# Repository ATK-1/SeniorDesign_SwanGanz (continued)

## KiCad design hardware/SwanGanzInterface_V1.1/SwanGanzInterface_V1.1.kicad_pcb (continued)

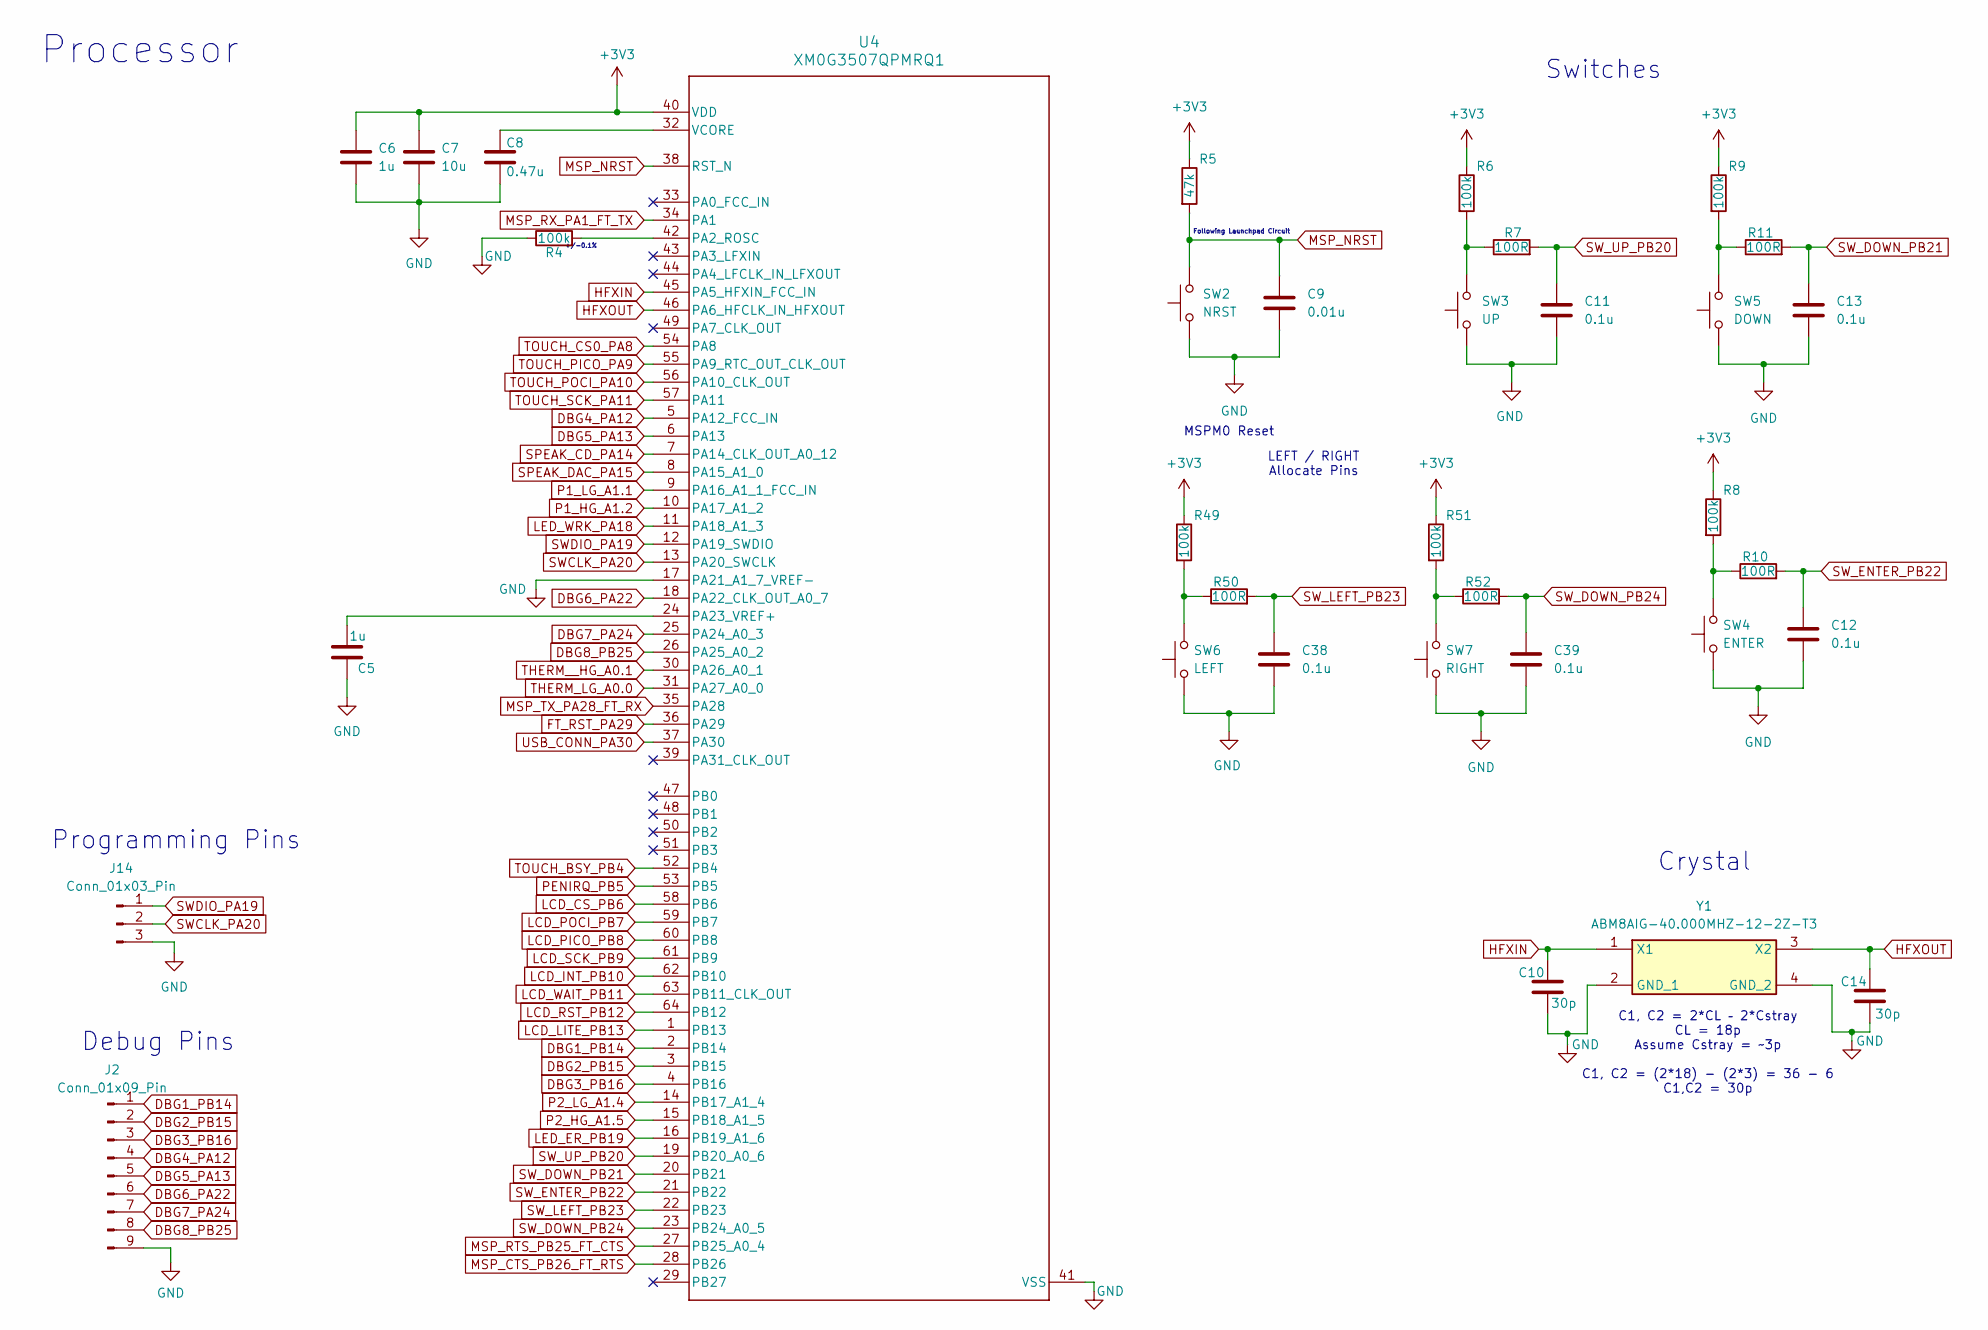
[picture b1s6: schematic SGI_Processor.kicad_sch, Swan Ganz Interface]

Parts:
C5, C6: 1u; C_0603_1608Metric
C7: 10u; C_1206_3216Metric
C8: 0.47u; C_0603_1608Metric_Pad1.08x0.95mm_HandSolder
C9: 0.01u; C_0603_1608Metric
C10, C14: 30p; C_0603_1608Metric
C11, C12, C13, C38, C39: 0.1u; C_0603_1608Metric
J2: Conn_01x09_Pin; PinSocket_1x09_P2.54mm_Vertical
J14: Conn_01x03_Pin; PinHeader_1x03_P2.54mm_Vertical
R4, R6, R8, R9, R49, R51: 100k; R_0603_1608Metric
R5: 47k; R_0603_1608Metric
R7, R10, R11, R50, R52: 100R; R_0603_1608Metric
SW2: NRST; SW_PUSH_6mm
SW3: UP; SW_PUSH_6mm
SW4: ENTER; SW_PUSH_6mm
SW5: DOWN; SW_PUSH_6mm
SW6: LEFT; SW_PUSH_6mm
SW7: RIGHT; SW_PUSH_6mm
U4: XM0G3507QPMRQ1; PM0064A-IPC_A
Y1: ABM8AIG-40.000MHZ-12-2Z-T3; ABM8AIG25000MHZ122ZT3; Manufacturer_Part_Number ABM8AIG-40.000MHZ-12-2Z-T3; Mouser Part Number 815-M8AIG-40-12-2ZT3

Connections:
+3V3: C6.1, C7.1, R5.1, R6.1, R8.1, R9.1, R49.1, R51.1, U4.40 (VDD); also elsewhere on the board
DBG1_PB14: J2.1, U4.2 (PB14)
DBG2_PB15: J2.2, U4.3 (PB15)
DBG3_PB16: J2.3, U4.4 (PB16)
DBG4_PA12: J2.4, U4.5 (PA12_FCC_IN)
DBG5_PA13: J2.5, U4.6 (PA13)
DBG6_PA22: J2.6, U4.18 (PA22_CLK_OUT_A0_7)
DBG7_PA24: J2.7, U4.25 (PA24_A0_3)
DBG8_PB25: J2.8, U4.26 (PA25_A0_2)
FT_RST_PA29: U4.36 (PA29); also elsewhere on the board
GND: C5.1, C6.2, C7.2, C8.2, C9.2, C10.1, C11.2, C12.2, C13.2, C14.1, C38.2, C39.2, J2.9, J14.3, R4.1, SW2.1, SW3.1, SW4.1, SW5.1, SW6.1, SW7.1, U4.17 (PA21_A1_7_VREF-), U4.41 (VSS), Y1.2 (GND_1), Y1.4 (GND_2); also elsewhere on the board
HFXIN: C10.2, U4.45 (PA5_HFXIN_FCC_IN), Y1.1 (X1)
HFXOUT: C14.2, U4.46 (PA6_HFCLK_IN_HFXOUT), Y1.3 (X2)
LCD_CS_PB6: U4.58 (PB6); also elsewhere on the board
LCD_INT_PB10: U4.62 (PB10); also elsewhere on the board
LCD_LITE_PB13: U4.1 (PB13); also elsewhere on the board
LCD_PICO_PB8: U4.60 (PB8); also elsewhere on the board
LCD_POCI_PB7: U4.59 (PB7); also elsewhere on the board
LCD_RST_PB12: U4.64 (PB12); also elsewhere on the board
LCD_SCK_PB9: U4.61 (PB9); also elsewhere on the board
LCD_WAIT_PB11: U4.63 (PB11_CLK_OUT); also elsewhere on the board
LED_ER_PB19: U4.16 (PB19_A1_6); also elsewhere on the board
LED_WRK_PA18: U4.11 (PA18_A1_3); also elsewhere on the board
MSP_CTS_PB26_FT_RTS: U4.28 (PB26); also elsewhere on the board
MSP_NRST: C9.1, R5.2, SW2.2, U4.38 (RST_N)
MSP_RTS_PB25_FT_CTS: U4.27 (PB25_A0_4); also elsewhere on the board
MSP_RX_PA1_FT_TX: U4.34 (PA1); also elsewhere on the board
MSP_TX_PA28_FT_RX: U4.35 (PA28); also elsewhere on the board
unnamed: R6.2, R7.1, SW3.2
unnamed: R8.2, R10.1, SW4.2
unnamed: R9.2, R11.1, SW5.2
unnamed: R49.2, R50.1, SW6.2
unnamed: R51.2, R52.1, SW7.2
unnamed: R4.2, U4.42 (PA2_ROSC)
unnamed: C5.2, U4.24 (PA23_VREF+)
unnamed: C8.1, U4.32 (VCORE)
P1_HG_A1.2: U4.10 (PA17_A1_2); also elsewhere on the board
P1_LG_A1.1: U4.9 (PA16_A1_1_FCC_IN); also elsewhere on the board
P2_HG_A1.5: U4.15 (PB18_A1_5); also elsewhere on the board
P2_LG_A1.4: U4.14 (PB17_A1_4); also elsewhere on the board
PENIRQ_PB5: U4.53 (PB5); also elsewhere on the board
SPEAK_CD_PA14: U4.7 (PA14_CLK_OUT_A0_12); also elsewhere on the board
SPEAK_DAC_PA15: U4.8 (PA15_A1_0); also elsewhere on the board
SWCLK_PA20: J14.2, U4.13 (PA20_SWCLK)
SWDIO_PA19: J14.1, U4.12 (PA19_SWDIO)
SW_DOWN_PB21: C13.1, R11.2, U4.20 (PB21)
SW_DOWN_PB24: C39.1, R52.2, U4.23 (PB24_A0_5)
SW_ENTER_PB22: C12.1, R10.2, U4.21 (PB22)
SW_LEFT_PB23: C38.1, R50.2, U4.22 (PB23)
SW_UP_PB20: C11.1, R7.2, U4.19 (PB20_A0_6)
THERM_LG_A0.0: U4.31 (PA27_A0_0); also elsewhere on the board
THERM__HG_A0.1: U4.30 (PA26_A0_1); also elsewhere on the board
TOUCH_BSY_PB4: U4.52 (PB4); also elsewhere on the board
TOUCH_CS0_PA8: U4.54 (PA8); also elsewhere on the board
TOUCH_PICO_PA9: U4.55 (PA9_RTC_OUT_CLK_OUT); also elsewhere on the board
TOUCH_POCI_PA10: U4.56 (PA10_CLK_OUT); also elsewhere on the board
TOUCH_SCK_PA11: U4.57 (PA11); also elsewhere on the board
USB_CONN_PA30: U4.37 (PA30); also elsewhere on the board

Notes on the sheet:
Switches
C1, C2 = 2*CL – 2*Cstray CL = 18p Assume Cstray = ~3p C1, C2 = (2*18) - (2*3) = 36 - 6 C1,C2 = 30p
Crystal
LEFT / RIGHT Allocate Pins
Debug Pins
MSPM0 Reset
Processor
+/-0.1%
Following Launchpad Circuit
Programming Pins

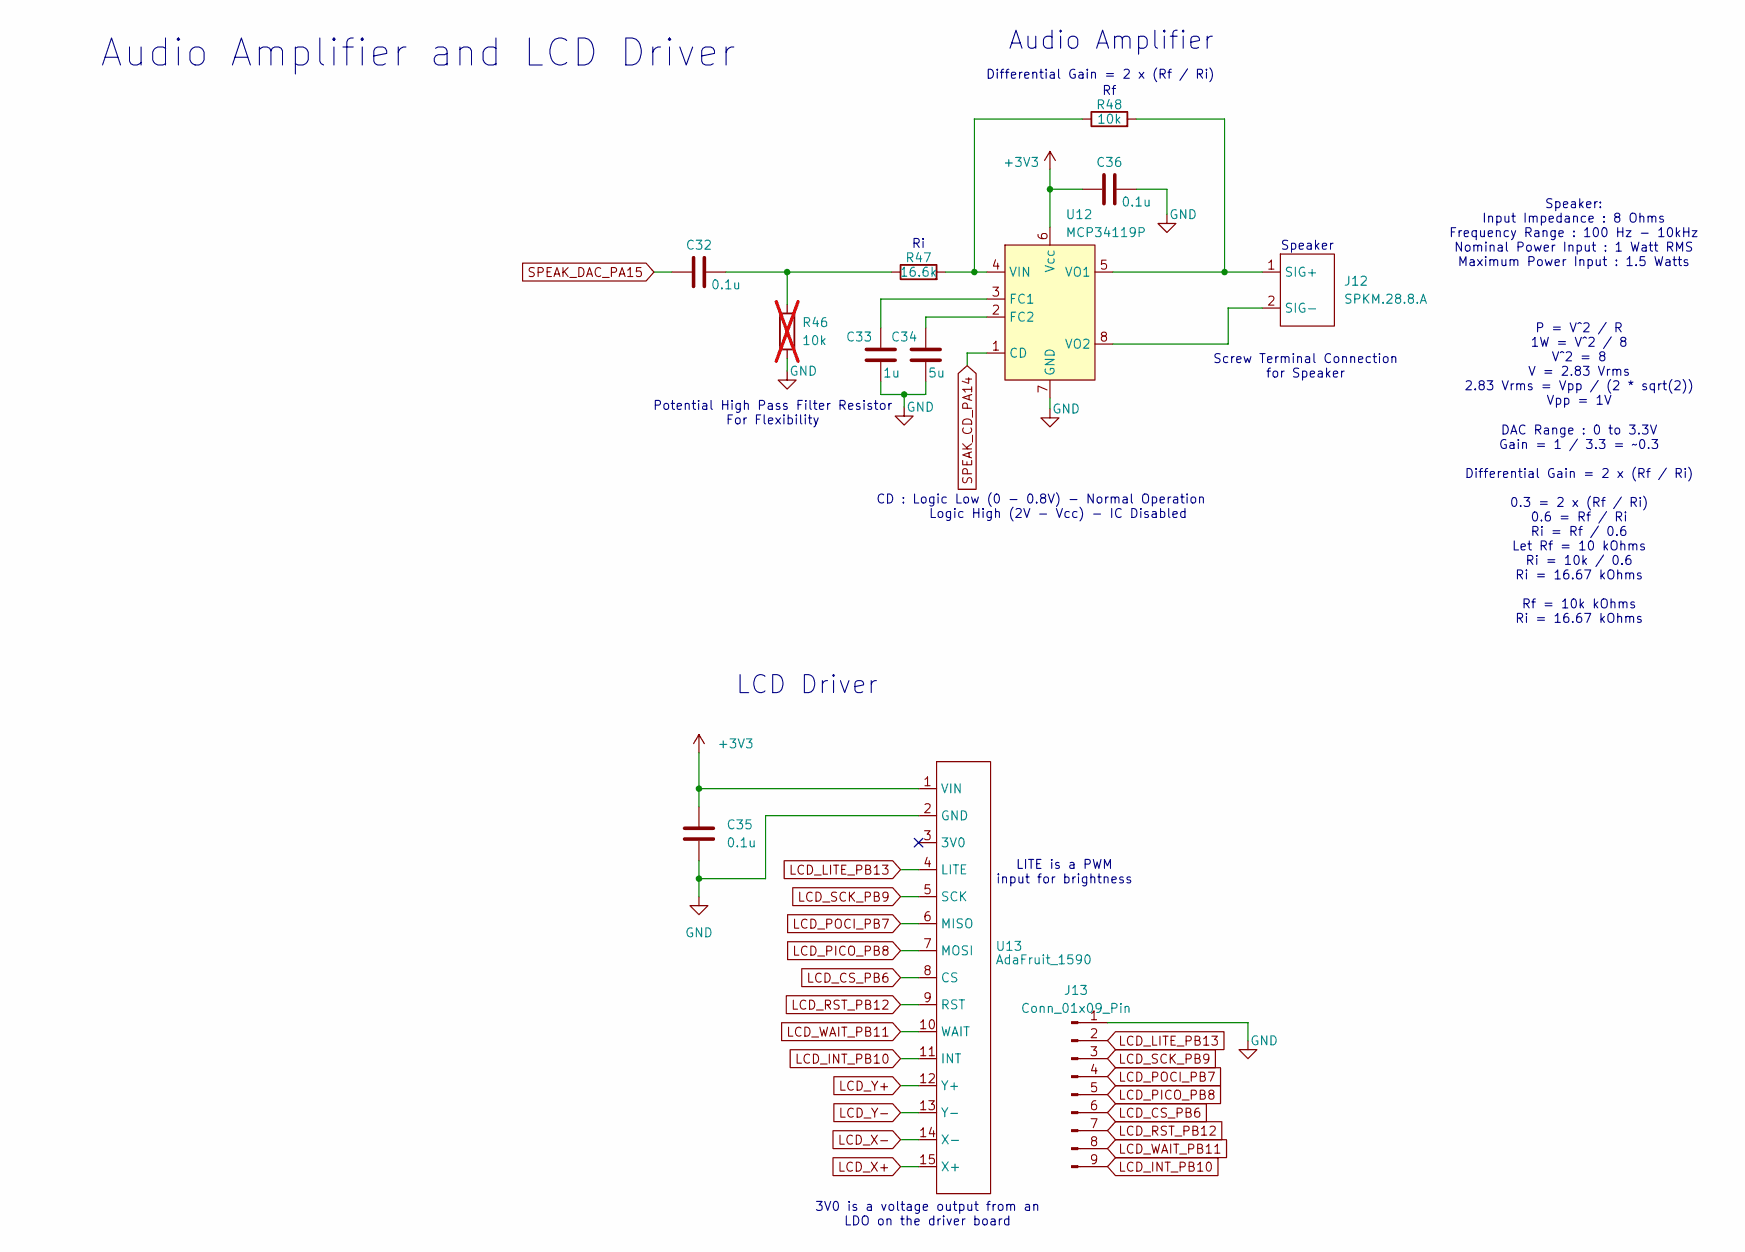
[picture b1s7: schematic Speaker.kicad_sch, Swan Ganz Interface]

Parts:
C32, C35, C36: 0.1u; C_0603_1608Metric
C33: 1u; C_0603_1608Metric
C34: 5u; C_1206_3216Metric
J12: SPKM.28.8.A; TerminalBlock_MaiXu_MX126-5.0-02P_1x02_P5.00mm
J13: Conn_01x09_Pin; PinHeader_1x09_P2.54mm_Vertical
R46: 10k; R_0603_1608Metric; not fitted
R47: 16.6k; R_0603_1608Metric
R48: 10k; R_0603_1608Metric
U12: MCP34119P; DIP-8_W7.62mm_LongPads
U13: AdaFruit_1590

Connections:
+3V3: C35.1, C36.1, U12.6 (Vcc), U13.1 (VIN); also elsewhere on the board
GND: C33.1, C34.1, C35.2, C36.2, J13.1, R46.2, U12.7 (GND), U13.2 (GND); also elsewhere on the board
LCD_CS_PB6: J13.6, U13.8 (CS); also elsewhere on the board
LCD_INT_PB10: J13.9, U13.11 (INT); also elsewhere on the board
LCD_LITE_PB13: J13.2, U13.4 (LITE); also elsewhere on the board
LCD_PICO_PB8: J13.5, U13.7 (MOSI); also elsewhere on the board
LCD_POCI_PB7: J13.4, U13.6 (MISO); also elsewhere on the board
LCD_RST_PB12: J13.7, U13.9 (RST); also elsewhere on the board
LCD_SCK_PB9: J13.3, U13.5 (SCK); also elsewhere on the board
LCD_WAIT_PB11: J13.8, U13.10 (WAIT); also elsewhere on the board
LCD_X+: U13.15 (X+); also elsewhere on the board
LCD_X-: U13.14 (X-); also elsewhere on the board
LCD_Y+: U13.12 (Y+); also elsewhere on the board
LCD_Y-: U13.13 (Y-); also elsewhere on the board
unnamed: C32.2, R46.1, R47.1
unnamed: J12.1 (SIG+), R48.2, U12.5 (VO1)
unnamed: J12.2 (SIG-), U12.8 (VO2)
unnamed: C33.2, U12.3 (FC1)
unnamed: C34.2, U12.2 (FC2)
unnamed: R47.2, R48.1, U12.4 (VIN)
SPEAK_CD_PA14: U12.1 (CD); also elsewhere on the board
SPEAK_DAC_PA15: C32.1; also elsewhere on the board

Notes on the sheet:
Audio Amplifier
CD : Logic Low (0 - 0.8V) - Normal Operation Logic High (2V - Vcc) - IC Disabled
Differential Gain = 2 x (Rf / Ri)
LITE is a PWM input for brightness
Audio Amplifier and LCD Driver
P = V^2 / R 1W = V^2 / 8 V^2 = 8 V = 2.83 Vrms 2.83 Vrms = Vpp / (2 * sqrt(2)) Vpp = 1V
Potential High Pass Filter Resistor For Flexibility
Speaker: Input Impedance : 8 Ohms Frequency Range : 100 Hz - 10kHz Nominal Power Input : 1 Watt RMS Maximum Power Input : 1.5 Watts
3V0 is a voltage output from an LDO on the driver board
Screw Terminal Connection for Speaker
Speaker
DAC Range : 0 to 3.3V Gain = 1 / 3.3 = ~0.3 Differential Gain = 2 x (Rf / Ri) 0.3 = 2 x (Rf / Ri) 0.6 = Rf / Ri Ri = Rf / 0.6 Let Rf = 10 kOhms Ri = 10k / 0.6 Ri = 16.67 kOhms Rf = 10k kOhms Ri = 16.67 kOhms
LCD Driver

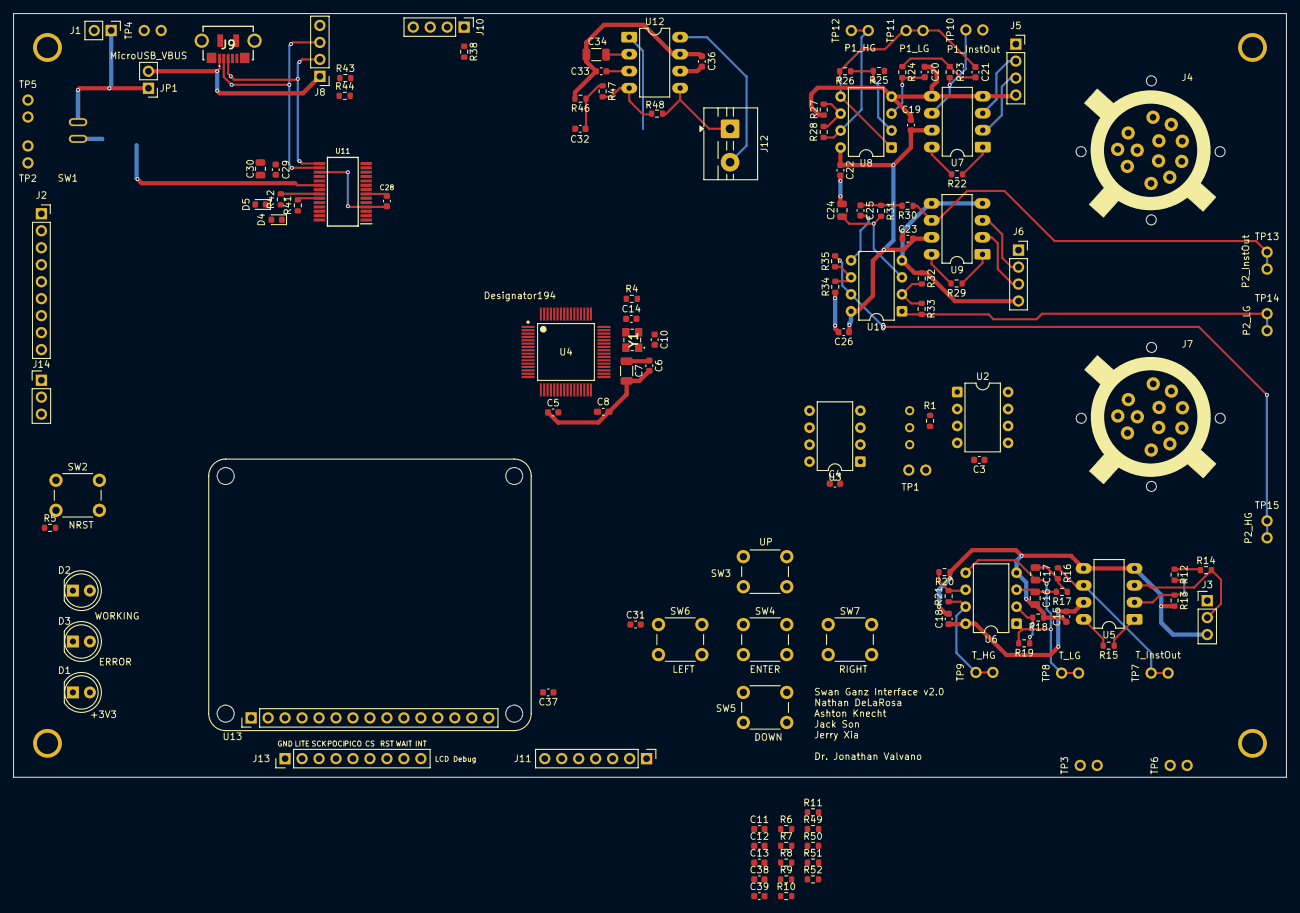
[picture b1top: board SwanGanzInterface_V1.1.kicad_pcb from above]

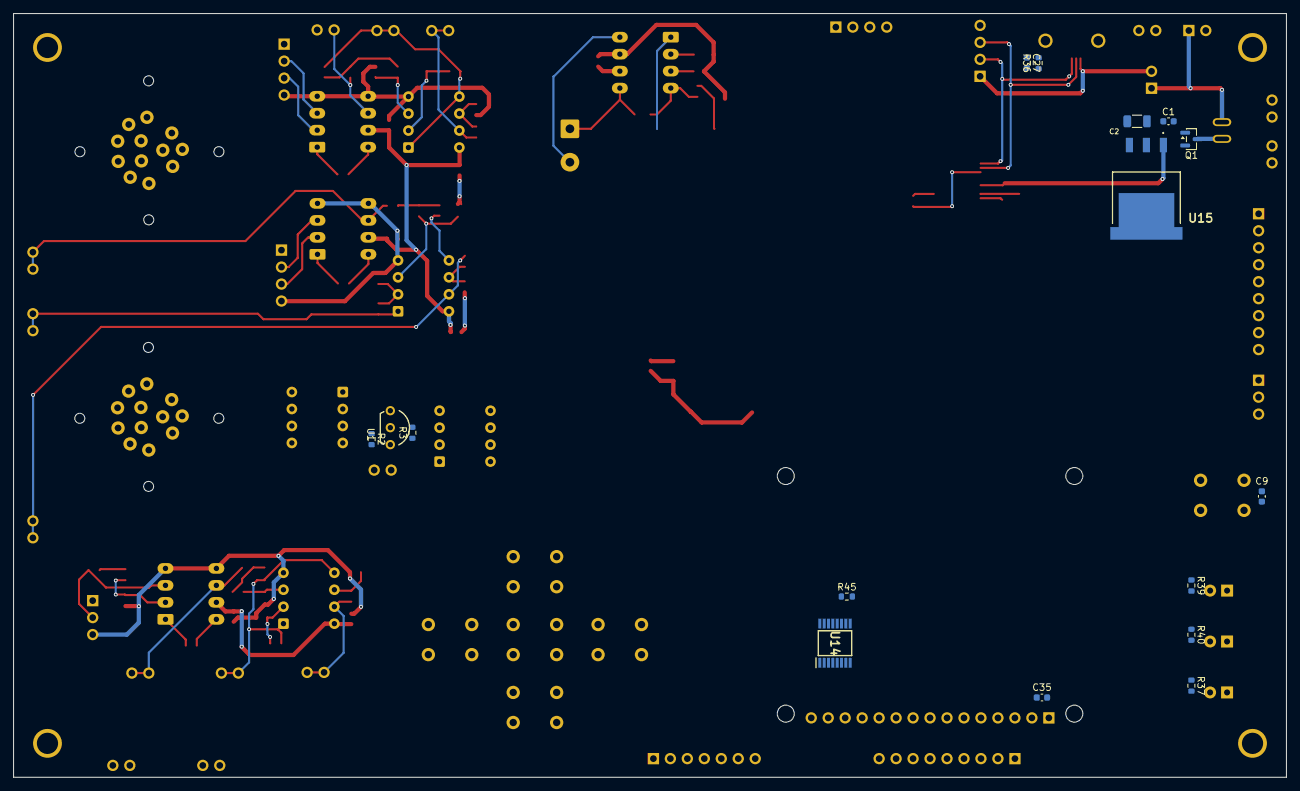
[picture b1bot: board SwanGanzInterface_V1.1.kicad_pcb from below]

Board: 4 copper layers, 190.5 x 114.3 mm, 154 parts (16 on the bottom side), 117 nets.

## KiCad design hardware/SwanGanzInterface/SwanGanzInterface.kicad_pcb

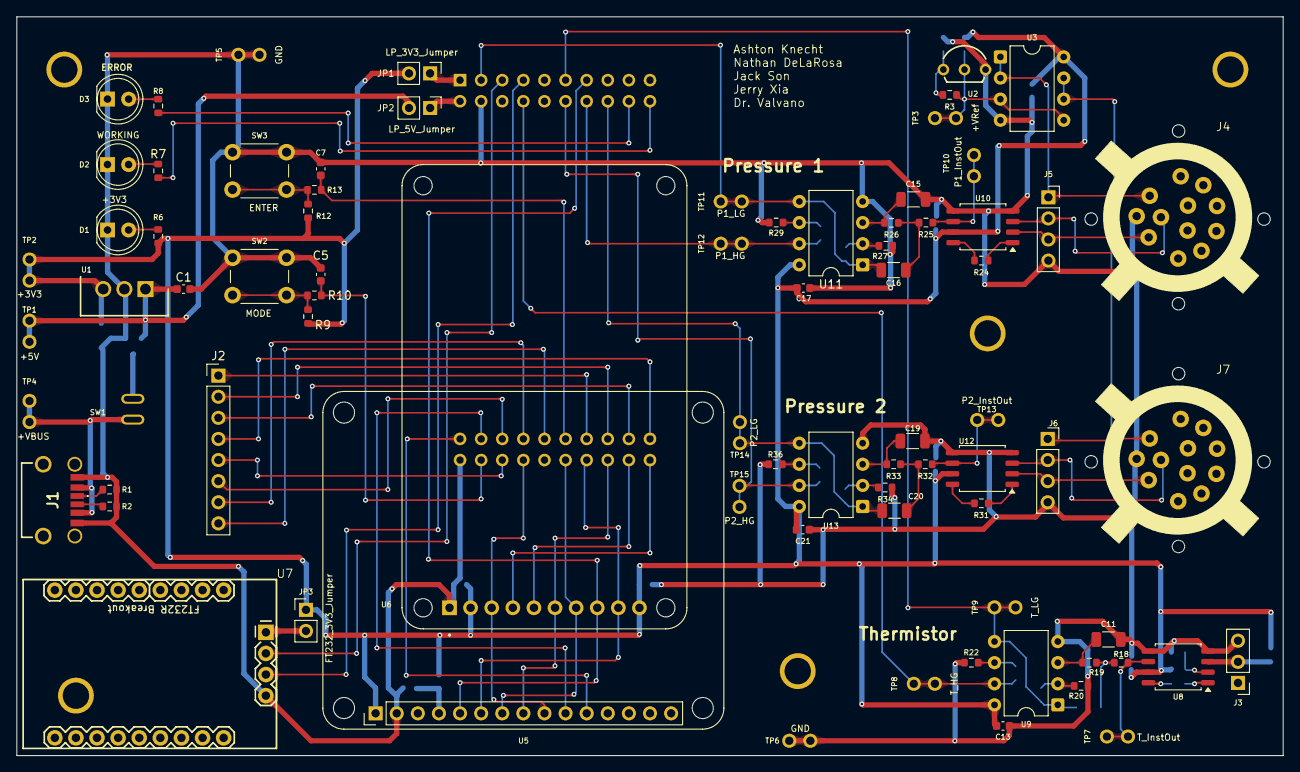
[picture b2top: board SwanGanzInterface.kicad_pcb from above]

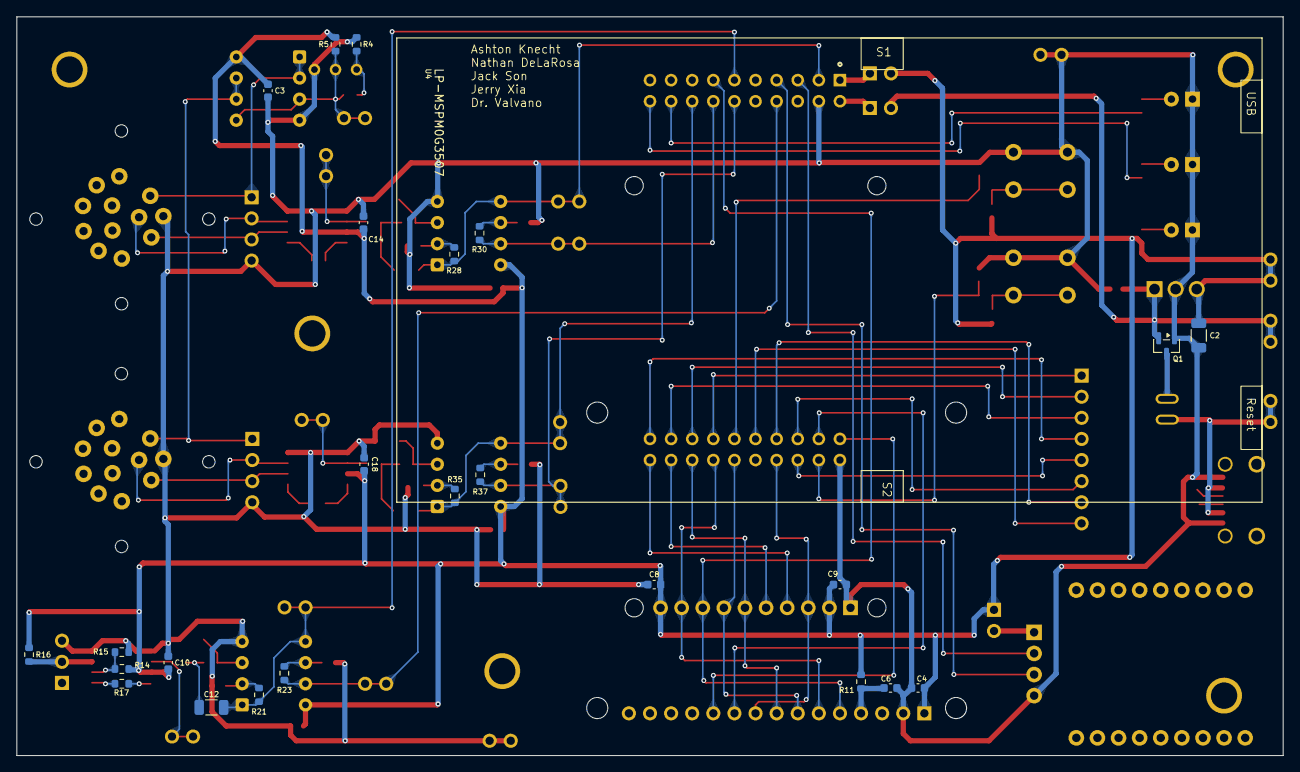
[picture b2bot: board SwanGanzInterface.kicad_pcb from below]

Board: 2 copper layers, 152.4 x 88.9 mm, 108 parts (25 on the bottom side), 76 nets.

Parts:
C1, C3, C4, C5, C6, C7, C8, C9, C10, C13, C14, C17, C18, C21: 0.1u; C_0603_1608Metric
C2: 10u; C_1206_3216Metric
C11, C12, C15, C16, C19, C20: 0.1u; C_1206_3216Metric
D1: +3V3; LED_D5.0mm
D2: WORKING; LED_D5.0mm
D3: ERROR; LED_D5.0mm
H1, H2, H3, H4, H5: MountingHole_4_40
J1: 2479774-1; 24797741
J2: Conn_01x08_Pin; PinHeader_1x08_P2.54mm_Vertical
J3: Conn_01x03_Pin; PinHeader_1x03_P2.54mm_Vertical
J4, J7: Pressure_Connector_1.1
J5, J6: Conn_01x04_Pin; PinSocket_1x04_P2.54mm_Vertical
JP1: LP_3V3_Jumper; PinHeader_1x02_P2.54mm_Vertical
JP2: LP_5V_Jumper; PinHeader_1x02_P2.54mm_Vertical
JP3: FT232_3V3_Jumper; PinHeader_1x02_P2.54mm_Vertical
Q1: SQ2389CES-T1_GE3; SOT-23
R1, R2: 5k1; R_0603_1608Metric
R3: 47k; R_0603_1608Metric
R4, R20, R21, R22, R23, R27, R28, R29, R34, R35, R36: 10k; R_0603_1608Metric
R5: 1k; R_0603_1608Metric
R6, R7, R8: 5k; R_0603_1608Metric
R9, R12, R14, R16: 100k; R_0603_1608Metric
R10, R13: 100R; R_0603_1608Metric
R11: 0R; R_0603_1608Metric
R15: 8k2; R_0603_1608Metric
R17: 65k5; R_0603_1608Metric
R18, R19: 160k; R_0603_1608Metric
R24, R31: 200R; R_0603_1608Metric
R25, R26, R32, R33: 32k; R_0603_1608Metric
R30, R37: 17k5; R_0603_1608Metric
SW1: Power_Switch; SW-T3-1A-A-A3-S1
SW2: MODE; SW_PUSH_6mm
SW3: ENTER; SW_PUSH_6mm
TP1: +5V; Testpoint_1x02_P2.54mm
TP2: +3V3; Testpoint_1x02_P2.54mm
TP3: +VRef; Testpoint_1x02_P2.54mm
TP4: +VBUS; Testpoint_1x02_P2.54mm
TP5, TP6: GND; Testpoint_1x02_P2.54mm
TP7: T_InstOut; Testpoint_1x02_P2.54mm
TP8: T_HG; Testpoint_1x02_P2.54mm
TP9: T_LG; Testpoint_1x02_P2.54mm
TP10: P1_InstOut; Testpoint_1x02_P2.54mm
TP11: P1_LG; Testpoint_1x02_P2.54mm
TP12: P1_HG; Testpoint_1x02_P2.54mm
TP13: P2_InstOut; Testpoint_1x02_P2.54mm
TP14: P2_LG; Testpoint_1x02_P2.54mm
TP15: P2_HG; Testpoint_1x02_P2.54mm
U1: LM2937ET-3.3_NOPB; TO254P470X1028X1955-3P
U2: LM4041CILPR; ti_LM4041CILPR
U3, U9, U11, U13: OPA2350; DIP-8_W7.62mm
U4: LP-MSPM0G3507; ti_LP_MSPM0G3507
U5: AdaFruit_1590
U6: Adafruit ST7735R; adafruit_st7735r
U7: FT232R; FT232R-Breakout
U8, U10, U12: INA122D; SOIC-8_5.3x5.3mm_P1.27mm

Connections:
+3V3: C2.1, C3.1, C4.1, C8.1, C9.1, C10.2, C13.1, C14.2, C17.1, C18.2, C21.1, JP1.2 (B), JP3.1 (A), R5.1, R6.1, R9.1, R11.1, R12.1, R14.1, R16.1, TP2.1 (A), TP2.2 (B), U1.3 (OUTPUT), U3.8 (V+), U5.1 (VIN), U6.2 (VCC), U6.10 (LITE), U8.7 (+VS), U9.8 (V+), U10.7 (+VS), U11.8 (V+), U12.7 (+VS), U13.8 (V+)
+5V: C1.1, JP2.2 (B), Q1.2 (S), TP1.1 (A), TP1.2 (B), U1.1 (INPUT)
+VBUS: J1.A9 (VBUS_1), J1.B9 (VBUS_2), SW1.1 (A), TP4.1 (A), TP4.2 (B)
+VRef: R3.1, R5.2, TP3.1 (A), TP3.2 (B), U2.2, U3.3 (+), U3.5 (+)
ADC_0.2: C16.2, R28.2, TP11.1 (A), TP11.2 (B), U4.J1_2 (PA25), U11.1, U11.5 (+)
ADC_0.3: R30.2, TP12.1 (A), TP12.2 (B), U4.J3_7 (PA24), U11.7
ADC_0.5: C12.2, R21.2, TP9.1 (A), TP9.2 (B), U4.J1_6 (PB24), U9.1, U9.5 (+)
ADC_0.7: R23.2, TP8.1 (A), TP8.2 (B), U4.J3_4 (PA22), U9.7
ADC_1.3: C20.2, R35.2, TP14.1 (A), TP14.2 (B), U4.J3_8 (PA17), U13.1, U13.5 (+)
ADC_1.5: R37.2, TP15.1 (A), TP15.2 (B), U4.J3_6 (PA18), U13.7
BACKLITE: C6.1, R11.2, U5.4 (LITE)
GND: C1.2, C2.2, C3.2, C4.2, C5.2, C6.2, C7.2, C8.2, C9.2, C10.1, C11.2, C13.2, C14.1, C15.2, C17.2, C18.1, C19.2, C21.2, D1.1 (K), D2.1 (K), D3.1 (K), J1.A12 (GND_1), J1.B12 (GND_2), J3.3, J4.4 (VDD), J5.4, J6.4, J7.4 (VDD), Q1.1 (G), R1.2, R2.2, R4.2, R15.2, R20.1, R22.1, R27.1, R29.1, R34.1, R36.1, SW2.1, SW3.1, TP5.1 (A), TP5.2 (B), TP6.1 (A), TP6.2 (B), U1.2 (GND), U2.3, U3.4 (V-), U4.J2_1 (GND), U4.J3_2 (GND), U5.2 (GND), U6.1 (GND), U7.4 (GND), U8.4 (-VS), U8.5 (REF), U9.4 (V-), U10.4 (-VS), U10.5 (REF), U11.4 (V-), U12.4 (-VS), U12.5 (REF), U13.4 (V-)
unnamed: C12.1, R18.2, R19.1
unnamed: C16.1, R25.2, R26.1
unnamed: C20.1, R32.2, R33.1
unnamed: D1.2 (A), R6.2
unnamed: D2.2 (A), R7.2
unnamed: D3.2 (A), R8.2
unnamed: J1.A5 (CC1), R1.1
unnamed: J1.B5 (CC2), R2.1
unnamed: J3.2, R16.2, U8.3 (+IN)
unnamed: JP1.1 (A), U4.J1_1 (+3.3V)
unnamed: JP2.1 (A), U4.J3_1 (+VBUS)
unnamed: JP3.2 (B), U7.1 (3V3)
unnamed: Q1.3 (D), SW1.2 (B)
unnamed: R3.2, R4.1, U2.1
unnamed: R9.2, R10.1, SW2.2
unnamed: R12.2, R13.1, SW3.2
unnamed: R14.2, R15.1, U8.2 (-IN)
unnamed: R17.1, U8.1 (RG+)
unnamed: R17.2, U8.8 (RG-)
unnamed: C11.1, R19.2, U9.3 (+)
unnamed: R20.2, R21.1, U9.2 (-)
unnamed: R22.2, R23.1, U9.6 (-)
unnamed: R24.1, U10.1 (RG+)
unnamed: R24.2, U10.8 (RG-)
unnamed: C15.1, R26.2, U11.3 (+)
unnamed: R27.2, R28.1, U11.2 (-)
unnamed: R29.2, R30.1, U11.6 (-)
unnamed: R31.1, U12.1 (RG+)
unnamed: R31.2, U12.8 (RG-)
unnamed: C19.1, R33.2, U13.3 (+)
unnamed: R34.2, R35.1, U13.2 (-)
unnamed: R36.2, R37.1, U13.6 (-)
P1_SIG+: J4.2 (SIG+), J5.2, U10.3 (+IN)
P1_SIG-: J4.3 (SIG-), J5.3, U10.2 (-IN)
P1_VCC: J4.1 (VCC), J5.1, U3.1, U3.2 (-)
P1__InstrOut: R25.1, TP10.1 (A), TP10.2 (B), U10.6 (OUT)
P2_SIG+: J6.2, J7.2 (SIG+), U12.3 (+IN)
P2_SIG-: J6.3, J7.3 (SIG-), U12.2 (-IN)
P2_VCC: J6.1, J7.1 (VCC), U3.6 (-), U3.7
P2__InstrOut: R32.1, TP13.1 (A), TP13.2 (B), U12.6 (OUT)
PA10: J2.1, U4.J4_7 (PA10)
PA11: J2.2, U4.J4_8 (PA11)
PA12: J2.3, U4.J4_9 (PA12)
PA13: J2.4, U4.J4_10 (PA13)
PA15: R7.1, U4.J3_10 (PA15)
PA16: R8.1, U4.J3_9 (PA16)
PA28: J2.6, U4.J4_3 (PA28)
PA31: J2.7, U4.J4_4 (PA31)
PB0: U4.J2_9 (PB0), U6.5 (CARD_CS)
PB1: U4.J4_2 (PB1), U5.10 (WAIT)
PB4: U4.J4_1 (PB4), U5.11 (INT)
PB6: U4.J2_8 (PB6), U5.8 (CS), U6.6 (TFT_CS)
PB7: U4.J2_7 (PB7), U5.6 (MISO), U6.9 (MISO)
PB8: U4.J2_6 (PB8), U5.7 (MOSI), U6.7 (MOSI)
PB9: U4.J1_7 (PB9), U5.5 (SCK), U6.8 (SCK)
PB12: C5.1, R10.2, U4.J2_2 (PB12)
PB13: C7.1, R13.2, U4.J4_6 (PB13)
PB15: U4.J2_4 (PB15), U5.9 (RST), U6.3 (RESET)
PB16: U4.J2_10 (PB16), U6.4 (D/C)
PB17: J2.5, U4.J2_3 (PB17)
PB20: J2.8, U4.J4_5 (PB20)
Therm__InstrOut: R18.1, TP7.1 (A), TP7.2 (B), U8.6 (OUT)
UART_Rx: U4.J1_3 (PA9/PB23), U7.2 (TXD)
UART_Tx: U4.J1_4 (PA8), U7.3 (RXD)

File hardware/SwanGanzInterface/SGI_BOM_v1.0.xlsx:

Reference | Part Number | Quantity | Mouser PN | Manufacturer | Value | Rating | Footprint | Tolerance | Type | Price for 1
C1, C3, C4, C5, C6, C7, C8, C9, C10, C13, C14, C17, C18, C21 | CC0603JRX7R9BB104 | 14 | 603-CC0603KRX7R9BB104 | YAGEO | 0.1uF | 50 VDC | 0603 | 0.05 | X7R | 0.1
C2 | C1206C106J3RACTU | 1 | 80-C1206C106J3RACTU | KEMET | 10uF | 25 VDC | 1206 | 0.05 | X7R | 0.94
C11, C12, C15, C16, C19, C20 | GRT31C5C1H104FA02L | 6 | 81-GRT31C5C1H104FA2L | Murata | 0.1uF | 25 VDC | 1206 | 0.01 | C0G | 0.91
D1, D2, D3 | HLMP-4700 | 3 | 630-HLMP-4700 | Broadcom/Avago | Red
Q1 | SQ2389CES-T1_GE3 | 1 | 78-SQ2389CES-T1_GE3 | Vishay/Siliconix | N/A | 40 Vds | SOT-23-3 | N/A | P-channel | 0.68
R1, R2 | CR0603-FX-5101ELF | 2 | 652-CR0603FX-5101ELF | Bourns | 5.1k | 75 V | 0603 | 0.01 | Thick film | 0.1
R3 | CRCW060347K0FKED | 1 | 71-CRCW060347K0FKED | Vishay | 47k | 75 V | 0603 | 0.01 | Thick film | 0.25
R4, R21, R22, R23, R24, R28, R29, R30, R35, R36, R37 | RCA060310K0FKEC | 11 | 71-RCA060310K0FKEC | Vishay/Draloric | 10k | 75 V | 0603 | 0.01 | thick film | 0.11
R5 | TNPW06031K00FHTA | 1 | 71-TNPW06031K00FHTA | Vishay | 1k | 75 V | 0603 | 0.01 | thin film | 0.39
R6, R7, R8 | 1879246-3 | 3 | 571-1879246-3 | TE Connectivity | 5k | 50 V | 0603 | 0.01 | thin film | 0.31
R9, R13, R15, R17 | RCA0603100KFKEC | 4 | 71-RCA0603100KFKEC | Vishay | 100k | 75 V | 0603 | 0.01 | Thick film | 0.11
R10, R14 | AC0603FRE07100RL | 2 | 603-AC0603FRE07100RL | YAGEO | 100 | 75 V | 0603 | 0.01 | Thick film | 0.1
R11, R12 | CRCW06030000Z0EI | 2 | 71-CRCW06030000Z0EI | Vishay | 0 | 75 V | 0603 | N/A | Thick film | 0.21
R16 | CR0603-FX-8201ELF | 1 | 652-CR0603FX-8201ELF | Bourns | 8.2k | 75 V | 0603 | 0.01 | Thick film | 0.1
R18 | RT0603DRD0765K5L | 1 | 603-RT0603DRD0765K5L | YAGEO | 65.5k | 75 V | 0603 | 5.0000000000000001E-3 | thin film | 0.1
R19, R20 | RT0603DRE07160KL | 2 | 603-RT0603DRE07160KL | YAGEO | 160k | 75 V | 0603 | 5.0000000000000001E-3 | thin film | 0.11
R25, R32 | RC0603FR-10200RL | 2 | 603-RC0603FR-10200RL | YAGEO | 200 | 75 V | 0603 | 0.01 | Thick film | 0.12
R26, R27, R33, R34 | RN73R1JTTD3202F50 | 4 | 660-RN73R1JTD3202F50 | KOA SPEER | 32k | 75 V | 0603 | 0.01 | thin film | 0.1
R31, R38 | CRCW060317K4FKEAC | 2 | 71-CRCW060317K4FKEAC | Vishay | 17.4k | 75 V | 0603 | 0.01 | thick film | 0.1
SW1 |  | 1
SW2, SW2 |  | 2
U8, U10, U12 | INA122UA/2K5 | 3 | 595-INA122UA/2K5 | Texas Instruments | N/A | N/A | SOIC-8 | N/A | IC | 6.72

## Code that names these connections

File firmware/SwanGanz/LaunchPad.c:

/* LaunchPad.c
 * Jonathan Valvano
 * November 3, 2025
 * Derived from gpio_toggle_output_LP_MSPM0G3507_nortos_ticlang
 */


#include <ti/devices/msp/msp.h>
#include "../inc/LaunchPad.h"

void Delay(uint32_t cycles){
    /* There will be a 2 cycle delay here to fetch & decode instructions
     * if branch and linking to this function */

    /* Subtract 2 net cycles for constant offset: +2 cycles for entry jump,
     * +2 cycles for exit, -1 cycle for a shorter loop cycle on the last loop,
     * -1 for this instruction */
#ifdef __GNUC__
    __asm(".syntax unified");
#endif
    __asm volatile(
"            SUBS  R0, R0, #2; \n"
"Delay_Loop: SUBS  R0, R0, #4; \n" // C=1 if no overflow
"            NOP;              \n" // C=0 when R0 passes through 0
"            BHS   Delay_Loop; \n"
        /* Return: 2 cycles */
    );
}
//  PA0 is red LED1,   index 0 in IOMUX PINCM table, negative logic
// PB22 is BLUE LED2,  index 49 in IOMUX PINCM table
// PB26 is RED LED2,   index 56 in IOMUX PINCM table
// PB27 is GREEN LED2, index 57 in IOMUX PINCM table
// PA18 is S1 positive logic switch,  index 39 in IOMUX PINCM table
// PB21 is S2 negative logic switch,  index 48 in IOMUX PINCM table
void ActivatePortA_B(void){
    // Reset two GPIO peripherals
    // RSTCLR
    //   bits 31-24 unlock key 0xB1
    //   bit 1 is Clear reset sticky bit
    //   bit 0 is reset gpio port
  GPIOA->GPRCM.RSTCTL = (uint32_t)0xB1000003;
  GPIOB->GPRCM.RSTCTL = (uint32_t)0xB1000003;

    // Enable power to two GPIO peripherals
    // PWREN
    //   bits 31-24 unlock key 0x26
    //   bit 0 is Enable Power
  GPIOA->GPRCM.PWREN = (uint32_t)0x26000001;
  GPIOB->GPRCM.PWREN = (uint32_t)0x26000001;

  Delay(24); // time for gpio to power up
}
// Initialize LEDs and switches
// Input: none
// Output:none
void LaunchPad_Init(void){
  ActivatePortA_B();

// PINCM
//   bit 25 is HiZ
//   bit 20 is drive strength (only available for PA10 PA11 PA28 PA31)
//   bit 18 is input enable control
//   bit 17 is pull up control
//   bit 16 is pull down control
//   bit 7 is PC peripheral connected, enable transparent data flow
//   bit 0 selects GPIO function
  IOMUX->SECCFG.PINCM[PA0INDEX]  = (uint32_t) 0x00000081;
  IOMUX->SECCFG.PINCM[PA18INDEX] = (uint32_t) 0x00050081; // input, pull down
  IOMUX->SECCFG.PINCM[PB21INDEX] = (uint32_t) 0x00060081; // input, pull up
  IOMUX->SECCFG.PINCM[PB22INDEX] = (uint32_t) 0x00000081;
  IOMUX->SECCFG.PINCM[PB26INDEX] = (uint32_t) 0x00000081;
  IOMUX->SECCFG.PINCM[PB27INDEX] = (uint32_t) 0x00000081;
// DOE31_0 Data output enable
  GPIOA->DOE31_0 |= RED1;
  GPIOB->DOE31_0 |= BLUE | RED | GREEN; // enable outputs
// DOUT31_0 read/write data output pins
  GPIOA->DOUT31_0 &= ~RED1; // LED1 off
  GPIOB->DOUT31_0 &= ~(BLUE | RED | GREEN); // clear LED2
}

// **** LaunchPad_InS1 *****
// Read S1,  positive logic switch on PA18
// return 0 if S1 is not pressed
//        0x00040000 if S1 is pressed
uint32_t LaunchPad_InS1(void){ uint32_t data;
  data = GPIOA->DIN31_0; // read all of Port A
  data = data & S1;      // select bit 18
  return data;
}
// **** LaunchPad_InS2 *****
// Read S2,  negative logic switch on PB21
// return 0 if S2 is not pressed
//        0x00200000 if S2 is pressed
uint32_t LaunchPad_InS2(void){ uint32_t data;
  data = GPIOB->DIN31_0; // read all of Port B
  data = data ^ S2;      // convert to positive logic
  return data & S2;      // select bit 21
}
// **** LaunchPad_LED1 *****
// Set LED1,  negative logic LED on PA0
// Input led=0 to PA0=1, turn off LED1
//       led=1 to PA0=0, turn on LED1
void LaunchPad_LED1(uint32_t led){uint32_t data;
  data = GPIOA->DOUT31_0; // read all of previous values
  data = data & ~0x01;    // clear bit 0
  data = data | (led^1);  // new value for bit 0
  GPIOA->DOUT31_0 = data; // change bit 0
}
// **** LaunchPad_LED1on *****
// Set LED1 on PA0, negative logic
// Makes PA0=0 to turn on LED
void LaunchPad_LED1on(void){
  GPIOA->DOUTCLR31_0 = RED1;
}
// **** LaunchPad_LED1off *****
// Set LED1 on PA0, negative logic
// Makes PA0=1 to turn off LED
void LaunchPad_LED1off(void){
  GPIOA->DOUTSET31_0 = RED1;
}
// **** LaunchPad_LED *****
// Set LED, 3-color positive logic LED on PB22,PB26,PB27
// Input led=0 to turn off LED
//       led bit 22 sets blue color
//       led bit 26 sets red color
//       led bit 27 sets green color
void LaunchPad_LED(uint32_t led){uint32_t data;
  data = GPIOB->DOUT31_0; // read all of previous values
  data = data & ~(BLUE|RED|GREEN); // clear bits 22,26,27
  data = data | led;      // new values for bits 22,26,27
  GPIOB->DOUT31_0 = data; // change bits 22,26,27
}
// **** LaunchPad_LEDwhite *****
// Set LED to white, 3-color positive logic LED on PB22,PB26,PB27
void LaunchPad_LEDwhite(void){
  GPIOB->DOUTSET31_0 = BLUE|RED|GREEN;
}
// **** LEDoff *****
// turn off LED, 3-color positive logic LED on PB22,PB26,PB27
void LaunchPad_LEDoff(void){
  GPIOB->DOUTCLR31_0 = BLUE|RED|GREEN;
}

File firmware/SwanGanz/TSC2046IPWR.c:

/*!
 * @file     TSC2056IPWR.c
 *
 * @mainpage TSC2056IPWR Resistive Touch Screen Driver
 *
 * @author   Ashton Knecht, Nathan DeLaRosa
 *
 *
 *
 * @section author Author
 *
 * Written by Ashton Knecht, Nathan DeLaRosa
 *
 */



#include <stdio.h>
#include <stdlib.h>
#include <ti/devices/msp/msp.h>
#include "../inc/LaunchPad.h"
#include "../inc/Clock.h"
#include "TSC2046IPWR.h"


/*
    Pin Allocation -
    SCLK - PA11
    CS0 - PA8
    PICO - PA9
    POCI - PA10
    BSY - PB4
    PENIRQ - PB5

    SPI Channel - SPI0
    Frame Requirments - 
        DCLK - Steady State Low => SPO = 0
        Data Captured on First DCLK edge transition (Rising Edge) => SPH = 0
*/


/*
    TSC2046 Command Structure
    Bit 7   :   (S)       Start Bit - Must be high for a control byte
    Bit 6-4 :   (A2-A0)   Channel Select Bits - Chooses multiplexer inputs, touch driver switches and refenerce inputs
    Bit 3   :   (MODE)    1 = 12-bit, 0 = 8-bit
    Bit 2   :   (SER/DFR) 1 = Single Ended (Not wanted), 0 = Differential
    Bit 1-0 :   (PD1-PD0) Power Down Mode Select

*/

// TSC2046_READ_X -> 0b_1_101_1_0_00
#define TSC2046_READ_X ((uint8_t) 0b11011000)

// TSC2046_READ_Y -> -b_1_001_1_0_00
#define TSC2046_READ_Y ((uint8_t) 0b10011000)

// TSC2046_Blank -> No high start bit thus TSC knows this is not a control byte
#define TSC2046_BLANK ((uint8_t) 0b00000000)


// CS Macros
#define TSC2046_CS_LOW()     (GPIOA->DOUTCLR31_0 = (1<<8))   // PA8 low
#define TSC2046_CS_HIGH()    (GPIOA->DOUTSET31_0 = (1<<8))   // PA8 high


// Static Helper Functions
static void TSC2046_SpiInit();
static void TSC2046_CS_Init();
static void TSC2046_SPI_Reset();


void TSC2046IPWR_Init() {
    TSC2046_SpiInit();
    // PENIRQ Pin
    IOMUX->SECCFG.PINCM[PB5INDEX]  = 0x00040081;
    // BUSY Pin (Not used but good to have)
    IOMUX->SECCFG.PINCM[PB4INDEX]  = 0x00040081;
}


// Derived from Dr. Valvano's SPI.c
static void TSC2046_SpiInit() {
    uint32_t busfreq =  Clock_Freq();

    // assumes GPIOA and GPIOB are reset and powered previously
    // RSTCLR to SPI0 peripherals
    //   bits 31-24 unlock key 0xB1
    //   bit 1 is Clear reset sticky bit
    //   bit 0 is reset gpio port
    SPI0->GPRCM.RSTCTL = 0xB1000003;

    // Enable power to SPI0 peripherals
    // PWREN
    //   bits 31-24 unlock key 0x26
    //   bit 0 is Enable Power
    SPI0->GPRCM.PWREN = 0x26000001;

    Clock_Delay(24); // time for gpio to power up

    SPI0->CLKSEL = 8; // SYSCLK
    // bit 3 SYSCLK
    // bit 2 MFCLK
    // bit 1 LFCLK
    //SPI0->CLKDIV = 0; // divide by 1
  
    // bits 2-0 n (0 to 7), divide by n+1
    //Set the bit rate clock divider to generate the serial output clock
    //     outputBitRate = (spiInputClock) / ((1 + SCR) * 2)
    //     8,000,000 = (16,000,000)/((0 + 1) * 2)
    //     8,000,000 = (32,000,000)/((1 + 1) * 2)
    //     6,666,667 = (40,000,000)/((2 + 1) * 2)
    //    10,000,000 = (40,000,000)/((1 + 1) * 2)
    //     8,000,000 = (80,000,000)/((4 + 1) * 2)
    //     8,000,000 = (Clock_Freq)/((m + 1) * 2)
    //     m = (Clock_Freq/16000000) - 1
    // if(busfreq <= 16000000) {
    //   SPI0->CLKCTL = 0; // frequency= busfreq/2
    // }
    // else if(busfreq == 40000000) {
    //   SPI0->CLKCTL = 1; // frequency= 10MHz
    // // SPI0->CLKCTL = 2; // frequency= 6.66MHz
    // }
    // else{
    //   SPI0->CLKCTL = busfreq/16000000 -1; // 8 MHz
    // }

    SPI0->CLKCTL = 399; //1 MHz


    // bit 14 CSCLR=0 not cleared
    // bits 13-12 CSSEL=0 CS0
    // bit 9 SPH = 0 => Output on DCK first edge transistion (Rising Edge)
    // bit 8 SPO = 0 => DCK steady state LOW
    // bit 7 PACKEN = 0 => No packing
    // bits 6-5 FRF = 01 (4 wire)
    // bits 4-0 n=7, data size is n+1 (8bit data)
    SPI0->CTL0 = (0 << 14) | (0 << 12) | (0 << 9) | (0 << 8) | (1 << 5) | (7 << 0);

    SPI0->CTL1 = 0x0015;
    // bits 29-24 RXTIMEOUT=0
    // bits 23-16 REPEATX=0 disabled
    // bits 15-12 CDMODE=0 manual
    // bit 11 CDENABLE=0 CS3
    // bit 7-5 =0 no parity
    // bit 4=1 MSB first
    // bit 3=0 POD (not used, not peripheral)
    // bit 2=1 CP controller mode
    // bit 1=0 LBM disable loop back
    // bit 0=1 enable SPI
    TSC2046_CS_Init();
    // configure PA11 PA9 PA10 as alternate SPI0 function
    // TODO: change this back to PA11
    IOMUX->SECCFG.PINCM[PA11INDEX]  = 0x00000083;  // SPI0 SCLK 
    IOMUX->SECCFG.PINCM[PA9INDEX]  = 0x00000083;  // SPI0 PICO
    IOMUX->SECCFG.PINCM[PA10INDEX]  = 0x00040083;  // SPI0 POCI
    // IOMUX->SECCFG.PINCM[PB15INDEX] = 0x00000081;  // GPIO output, LCD !RST
    // GPIOB->DOE31_0 |= (1<<15);    // PB15 is LCD !RST
    // GPIOB->DOUTSET31_0 = (1<<15); // !RST = 1, RS=1

    TSC2046Pos_t initialPos = TSC2046IPWR_ReadRawPosition();
}


// CS0 - PA8 - Negative Logic
static void TSC2046_CS_Init() {
  IOMUX->SECCFG.PINCM[PA8INDEX]  = (uint32_t) 0x00000081;
  GPIOA->DOE31_0 |= (1 << 8);
  GPIOA->DOUTSET31_0 = (1 << 8);
}


//---------TSC2046_OutByte------------
// Output: None
// Input: 8-bit data to be transmitted to TSC2046
// Transmits a SPI byte to TSC2046 without a return
void TSC2046IPWR_OutByte(uint8_t data) {
    uint8_t response;
    // TSC2046_CS_LOW();
    while((SPI0->STAT&0x10) == 0x10){}; // spin if SPI busy
    SPI0->TXDATA = data;
    // while((SPI1->STAT&0x04) == 0x04){}; // spin SPI RxFifo empty
    while((SPI0->STAT&0x10) == 0x10) {}; // spin if SPI busy
    // TSC2046_CS_HIGH();
    response = SPI0->RXDATA; // has no meaning, flush
}


//---------TSC2046_OutByte------------
// Output: 8-bit read from TSC2046
// Input: 8-bit data to be transmitted to TSC2046
// Transmits a SPI byte to TSC2046 with a read return byte
uint8_t TSC2046IPWR_OutReadByte(uint8_t data) {
    // TSC2046_CS_LOW();
    while((SPI0->STAT&0x10) == 0x10){}; // spin if SPI busy
    SPI0->TXDATA = data;
    // while((SPI1->STAT&0x04) == 0x04){}; // spin SPI RxFifo empty
    while((SPI0->STAT&0x10) == 0x10) {}; // spin if SPI busy
    // TSC2046_CS_HIGH();
    return SPI0->RXDATA; // has no meaning, flush
}


//---------TSC2046IPWR_ReadRawPosition------------
// Output: TSC2046Pos_t - Raw 12-bit ADC values for both x and y directions
// Input: None
// Reads X and Y position returning the raw 12-bit adc value of both through the TSC2046Pos_t struct
TSC2046Pos_t TSC2046IPWR_ReadRawPosition() {
    TSC2046Pos_t result;
    result.xpos = 0;
    result.ypos = 0;
    TSC2046_CS_LOW();
    // Send Control Byte to specify x read
    TSC2046IPWR_OutByte(TSC2046_READ_X);                                        // Send X control byte
    result.xpos = ((uint32_t)TSC2046IPWR_OutReadByte(TSC2046_BLANK)) << 5;      // Read high 7 X bits
    result.xpos |= ((uint32_t)TSC2046IPWR_OutReadByte(TSC2046_READ_Y)) >> 3;    // Read low 5  X bits and send Y control byte
    result.ypos = ((uint32_t)TSC2046IPWR_OutReadByte(TSC2046_BLANK)) << 5;      // Read high 7 Y bits
    result.ypos |= ((uint32_t)TSC2046IPWR_OutReadByte(TSC2046_BLANK)) >> 3;     // Read low 5 Y bits

    TSC2046_CS_HIGH();
    return result;
}



// ---------- TSC2046IWR_PollTouch ----------
// Outputs: 1 => Screen Touch, 0 => No Screen Touch
// Inputs: None
// Checks for a screen touch -- assumes screen is in PD = 00 mode (Polling on PENIRQ)
uint32_t TSC2046IPWR_PollTouch() {
    // Check PENIRQ pin (PB5) -> Negative Logic
    return !(GPIOB->DIN31_0 & 0x0020);
}

// ---------- TSC2046IWR_GetX ----------
// Outputs: ADC value for screen touch in the X direction
// Inputs: None
// Transmits the read x byte and 2 null bytes to recieve x position of a touch
uint32_t TSC2046IPWR_GetX() {
    uint16_t x = 0;
    TSC2046_CS_LOW();
    // Send Control Byte to specify x read
    TSC2046IPWR_OutByte(TSC2046_READ_X);   
    x = ((uint32_t)TSC2046IPWR_OutReadByte(TSC2046_BLANK)) << 7;      // Read high 7 X bits
    x |= ((uint32_t)TSC2046IPWR_OutReadByte(TSC2046_BLANK)) >> 3;    // Read low 5  X bits 
    TSC2046_CS_HIGH();

    return x;
}


// ---------- TSC2046IWR_GetY ----------
// Outputs: ADC value for screen touch in the X direction
// Inputs: None
// Transmits the read y byte and 2 null bytes to recieve y position of a touch
uint32_t TSC2046IPWR_GetY() {
    uint32_t y = 0;
    TSC2046_CS_LOW();
    // Send Control Byte to specify y read
    TSC2046IPWR_OutByte(TSC2046_READ_Y);                             // Send X control byte
    y = ((uint32_t)TSC2046IPWR_OutReadByte(TSC2046_BLANK)) << 5;     // Read high 7 X bits
    y |= ((uint32_t)TSC2046IPWR_OutReadByte(TSC2046_BLANK)) >> 3;    // Read low 5  X bits 
    TSC2046_CS_HIGH();
    return y;
}
